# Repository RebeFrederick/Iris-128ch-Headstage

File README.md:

# Iris-128

Open-source 128-channel headstages for neural stimulation and recording.

*The publication of this work can be found at DOI 10.1088/1741-2552/ae1876. The raw data files corresponding to the publication can be found at https://doi.org/10.17605/OSF.IO/XS2PU.*

> [!NOTE]
> Detail documentation and user guides can be found at https://docs.openic.org/iris-128.

| Type | Description |
| :--: | :---------- |
| [Iris-128B](iris-128b/README.md)  | Fully bidirectional headstage with recording or stimulation across all 128 electrode channels. |
| [Iris-128S](iris-128s/README.md) | Selective stimulation headstage with recording from 128 channels and stimulation on 16 simultaneous channels out of 32 available stimulation channels. |
| [Thin-film electrode](thin-film/README.md) | 128 channel surface array used as a test platform for the headstages. |

## File Structure

| Folder  | Description    |
| :-----: | :------------- |
| iris-128b | Project, design, and fabrication files related to Iris-128B Neural Interface System. |
| iris-128s | Project, design, and fabrication files related to Iris-128S Neural Interface System. |
| thin-film    | Design files related to the microelectrode test platform. |
| images    | image files used in README and description files. |

## EDA Tools used in the Development

| EDA Tool     | Version | Usage           |
| :----------: | :-----: | :-------------- |
| KiCad        | 8.0.5   | Design of PCBs. |
| KiCad        | 9.0.3   | Design of PCBs. |
| STM32CubeIDE | 1.16.0  | Design of firmware for MCU. |

## Developers

* Deku Lab, University of Oregon, Eugene, OR
* OpenIC, Eagan, MN

## License

Copyright Manuel Monge, Emma Jacobs 2025.

This source describes Open Hardware and is licensed under CERN-OHL-P v2.

You may redistribute and modify this source and make products using it under the terms of the CERN-OHL-P v2 ([https:/cern.ch/cern-ohl](https:/cern.ch/cern-ohl)). This source is distributed WITHOUT ANY EXPRESS OR IMPLIED WARRANTY, INCLUDING OF MERCHANTABILITY, SATISFACTORY QUALITY AND FITNESS FOR A PARTICULAR PURPOSE. Please see the CERN-OHL-P v2 for applicable conditions.

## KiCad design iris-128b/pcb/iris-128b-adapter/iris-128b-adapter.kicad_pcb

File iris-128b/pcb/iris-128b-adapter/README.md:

# Iris-128B-adapter

*Fig. 1. Adapter connections.*

## Description

`IRIS-128B-ADAPTER`.

### Overview

**Adapter board**.

This is a board with no active components on it. It's purpose is simply to route the connections from the Iris-128B headstage to the power supply, and the four ports on the Intan RHS controller. It also has some header pins intended for testing the SPI connections.

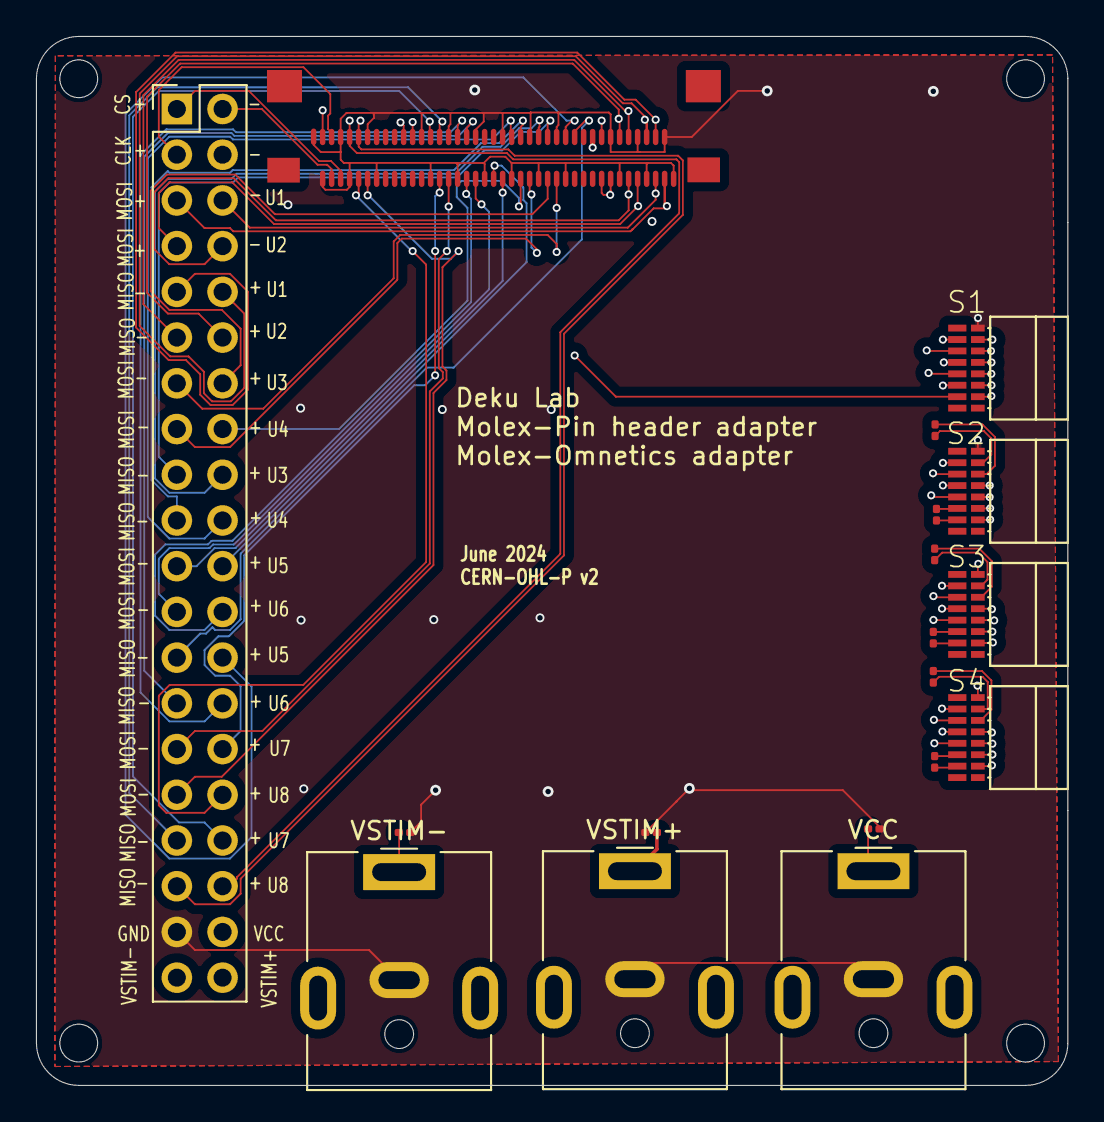
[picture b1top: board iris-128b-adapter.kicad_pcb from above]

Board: 4 copper layers, 57.3 x 58.3 mm, 22 parts (0 on the bottom side), 38 nets.

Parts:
C1, C2, C3: 10 uF; C_0201_0603Metric
H1, H2, H3, H4: MountingHole; MountingHole_2.1mm
J1: Conn_01x40_Pin; PinHeader_2x20_P2.54mm_Vertical
J2: Conn_02x40_Row_Letter_First; molex
R1, R2, R3, R4, R5, R6: R_US; R_0201_0603Metric
S1, S2, S3, S4: OMNETICS_PZN-16-AA
VCC: Barrel_Jack_MountingPin; BarrelJack_CUI_PJ-063AH_Horizontal
VSTIM+: Barrel_Jack_MountingPin; BarrelJack_CUI_PJ-063AH_Horizontal
VSTIM-: Barrel_Jack_MountingPin; BarrelJack_CUI_PJ-063AH_Horizontal

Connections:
/CS+: J1.2, J2.a39, S1.B6 (~CS+)
/CS-: J1.1, J2.a38, S1.B7 (~CS-)
/S1_MISO1+: J1.10, J2.b3, S1.T7 (MISO1+)
/S1_MISO1-: J1.9, J2.b2, S1.T6 (MISO1-)
/S1_MISO2+: J1.12, J2.b6, S1.B2 (MISO2+)
/S1_MISO2-: J1.11, J2.b5, S1.B3 (MISO2-)
/S1_MOSI1+: J1.6, J2.a3, S1.T5 (MOSI1+)
/S1_MOSI1-: J1.5, J2.a2, S1.T4 (MOSI1-)
/S1_MOSI2+: J1.8, J2.a6, S1.B4 (MOSI2+)
/S1_MOSI2-: J1.7, J2.a5, S1.B5 (MOSI2-)
/S2_MISO1+: J1.18, J2.b15, S2.T7 (MISO1+)
/S2_MISO1-: J1.17, J2.b14, S2.T6 (MISO1-)
/S2_MISO2+: J1.20, J2.b18, S2.B2 (MISO2+)
/S2_MISO2-: J1.19, J2.b17, S2.B3 (MISO2-)
/S2_MOSI1+: J1.14, J1.16, J2.a15, J2.a18, S2.B4 (MOSI2+), S2.T5 (MOSI1+)
/S2_MOSI1-: J1.13, J1.15, J2.a14, J2.a17, S2.B5 (MOSI2-), S2.T4 (MOSI1-)
/S3_MISO1+: J1.26, J2.b12, J2.b21, S3.T7 (MISO1+)
/S3_MISO1-: J1.25, J2.b11, J2.b20, S3.T6 (MISO1-)
/S3_MISO2+: J1.28, J2.b24, S3.B2 (MISO2+)
/S3_MISO2-: J1.27, J2.b23, S3.B3 (MISO2-)
/S3_MOSI1+: J1.22, J2.a21, S3.T5 (MOSI1+)
/S3_MOSI1-: J1.21, J2.a20, S3.T4 (MOSI1-)
/S3_MOSI2+: J1.24, J2.a24, S3.B4 (MOSI2+)
/S3_MOSI2-: J1.23, J2.a23, S3.B5 (MOSI2-)
/S4_MISO1+: J1.34, J2.b27, S4.T7 (MISO1+)
/S4_MISO1-: J1.33, J2.b26, S4.T6 (MISO1-)
/S4_MISO2+: J1.36, J2.b36, S4.B2 (MISO2+)
/S4_MISO2-: J1.35, J2.b35, S4.B3 (MISO2-)
/S4_MOSI1+: J1.30, J2.a27, S4.T5 (MOSI1+)
/S4_MOSI1-: J1.29, J2.a26, S4.T4 (MOSI1-)
/S4_MOSI2+: J1.32, J2.a36, S4.B4 (MOSI2+)
/S4_MOSI2-: J1.31, J2.a35, S4.B5 (MOSI2-)
/SCLK+: J1.4, J2.b39, S1.T3 (SCLK+)
/SCLK-: J1.3, J2.b38, S1.T2 (SCLK-)
GND: C1.2, C2.2, C3.2, J1.37, J2.a1, J2.a4, J2.a7, J2.a13, J2.a16, J2.a19, J2.a22, J2.a25, J2.a28, J2.a34, J2.a37, J2.a40, J2.b1, J2.b4, J2.b7, J2.b13, J2.b16, J2.b19, J2.b22, J2.b25, J2.b28, J2.b34, J2.b37, J2.b40, S1.B8 (GND), S2.B8 (GND), S3.B8 (GND), S4.B8 (GND), VCC.2, VSTIM+.2, VSTIM-.2
VCC: C1.1, J1.38, J2.a8, J2.a9, VCC.1
VSTIM+: C2.1, J1.40, J2.b8, J2.b29, VSTIM+.1
VSTIM-: C3.1, J1.39, J2.b9, J2.b30, VSTIM-.1

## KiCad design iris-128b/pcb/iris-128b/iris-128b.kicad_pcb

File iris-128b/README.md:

# Iris-128B
> [!NOTE]
> Detail documentation and user guides can be found at https://docs.openic.org/iris-128/iris-128b.

<br>

*Fig. 1. Iris-128B Neural Interface.*

## Description

### Overview

A **128-channel neural interface capable of stimulation and recording**.

This project develops a system that can stimulate and record from 128 channels using commercially available ICs and integrates into existing commercially available controllers (Intan RHS system). This can be used for small animal, anesthetized electrophysiology, non-human primates, or could be applied to clinical, intraoperative human use cases.

### Iris 128B Architecture

*The Iris 128B system consists of 2 boards: the headstage and the adapter.*

* The **headstage** is a small electronic system placed on top of or near the electrophysiological signals being recorded.
* It uses **commercially available off-the-shelf components**.
* The **adapter board** receives signals from the headstage (through the 80 pin nanopitch Molex connector and cable) and breaks them out into cables that interface with the **Intan Rec/Stim Controller**.

*Fig. 2. System architecture.*

<br>

## Specifications

* Recording and stimulation from all 128 channels.
* Compatible with Intan Recording Controller and Intan Stim/Record Controller.
* *SEAM8 Samtec* connector for interfacing with 128-ch electrode array and compatible with *BlackRock Cereplex E headstages*.
* The *headstage* has a size of 27 x 44 mm$^2$.
* *Molex Nanopitch 76-POS* connector to interface with *Adapter* board through a single cable.
* *Adapter* board draws power from power supply.
* The *adapter* has a size of 57 x 58 mm$^2$.

<br>

## File Structure

### Top Folders: /iris-128b

| Folder  | Subfolders                  | Description    |
| :-----: | :-------------------------- | :------------- |
| pcb | iris-128b <br> iris-128b-adapter <br> libraries | Project, design, and fabrication files related to Iris-128B headstage PCB fabrication and assembly. <br> Project, design, and fabrication files related to Iris-128B adapter PCB fabrication and assembly. <br> Ki-Cad libraries and common files used in PCBs |

<br>

### PCB Folders: /iris-128b/pcb/

| Folder  | Subfolders                  | Description    |
| :-----: | :-------------------------- | :------------- |
| . / |  | Project and design files related to Iris128B. |
| manufacturing |  gerber <br> assembly <br> bom | Gerber files for fabrication of `Iris-PCB`. <br> Assembly files for `Iris-PCB`. <br> Bill of Materials for `Iris-PCB`. |

<br>

## File Types

| File | Folder | Description |
| :--- | :----- | :---------- |
| README.md | iris-128x | Description of Iris-128X system. |
| kicad-files | iris-128x / pcb / | Ki-Cad project and design files. |
| gerber-files | iris-128x / pcb / manufacturing / gerber | Gerber files. |
| iris-128x-all-pos.csv | iris-128x / pcb / manufacturing / assembly | Assembly files in `csv` format.|
| iris-128x_bom.csv | iris-128x / pcb / manufacturing / bom | Bill of materials in `csv` format. |
| symbol-libraries | iris-128x / pcb / libraries | Ki-Cad symbol libraries used in PCBs. |
| footprint-libraries | iris-128x / pcb / libraries | Ki-Cad footprint libraries used in PCBs. |

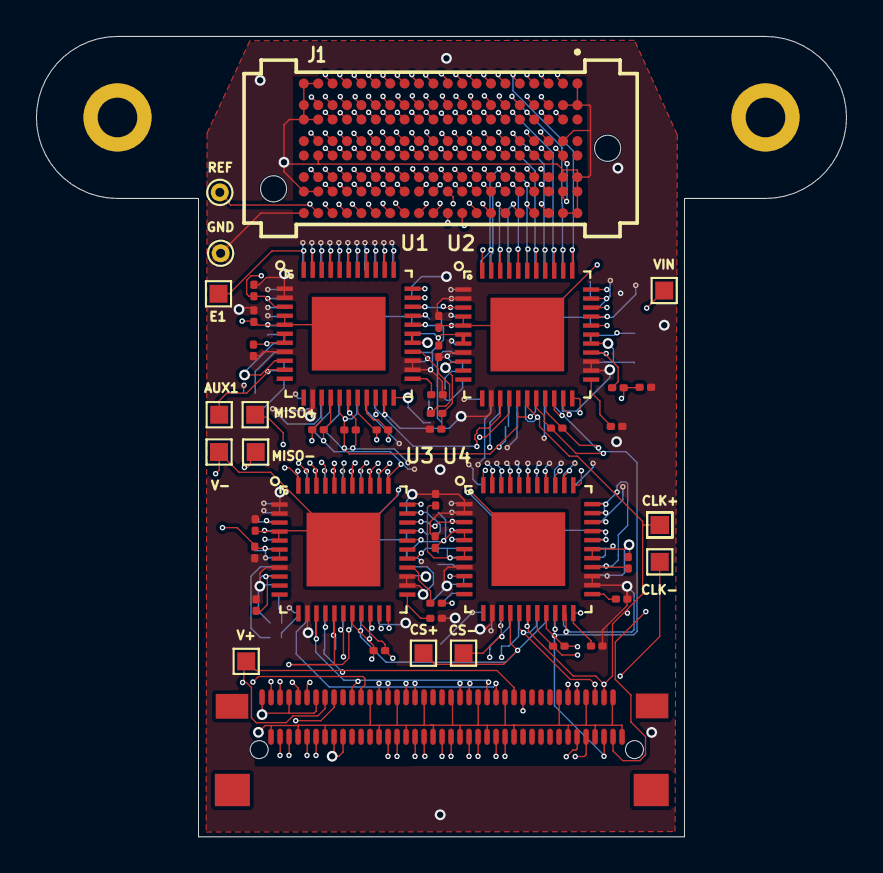
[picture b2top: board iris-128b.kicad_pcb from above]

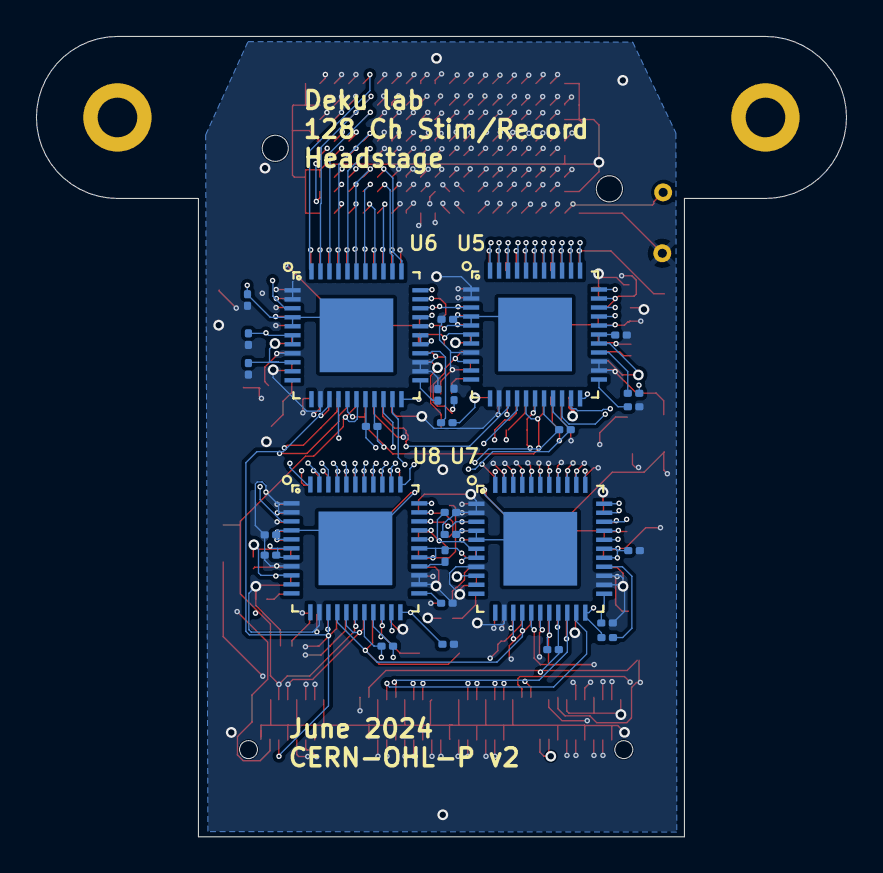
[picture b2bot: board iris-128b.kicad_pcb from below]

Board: 8 copper layers, 45.0 x 44.5 mm, 77 parts (28 on the bottom side), 184 nets.

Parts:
AUX1: TestPoint; TestPoint_Pad_1.0x1.0mm
C1, C2, C3, C4, C5, C6, C7, C8, C9, C10, C11, C12, C13, C14, C15, C16, C17, C18, C19, C20, C21, C22, C23, C24: 100 nF; C_0201_0603Metric
C25, C26, C27, C28, C29, C30, C31, C32: 10 nF; C_0201_0603Metric
CLK+: TestPoint; TestPoint_Pad_1.0x1.0mm
CLK+#2: TestPoint; TestPoint_Pad_1.0x1.0mm
CLK-: TestPoint; TestPoint_Pad_1.0x1.0mm
CS+: TestPoint; TestPoint_Pad_1.0x1.0mm
CS-: TestPoint; TestPoint_Pad_1.0x1.0mm
E1: TestPoint; TestPoint_Pad_1.0x1.0mm
GND: TESTPOINT_SMALL; TestPoint_THTPad_D1.0mm_Drill0.5mm
H1, H2: MountingHole; MountingHole_2.2mm_M2_DIN965_Pad
J1: SEAM8-20-S02.0-X-08-3; SAMTEC_SEAM8-20-S02.0-X-08-3
J2: Conn_02x40_Row_Letter_First; molex
LVDS1, LVDS2, LVDS3, LVDS4, LVDS5, LVDS6, LVDS7, LVDS8: 0; R_0201_0603Metric
MISO+: TestPoint; TestPoint_Pad_1.0x1.0mm
MISO-: TestPoint; TestPoint_Pad_1.0x1.0mm
R1: 0; R_0201_0603Metric
R2, R3, R4, R5, R6, R7, R8, R9, R10, R11: 100; R_0201_0603Metric
REF: TESTPOINT_SMALL; TestPoint_THTPad_D1.0mm_Drill0.5mm
U1, U2, U3, U4, U5, U6, U7, U8: QFN44_7_X_7
V+: TestPoint; TestPoint_Pad_1.0x1.0mm
V-: TestPoint; TestPoint_Pad_1.0x1.0mm
VIN: VCC; TestPoint_Pad_1.0x1.0mm

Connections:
/CS+: CS+.1, J2.b39, R10.1, U1.15 (~CS+), U2.15 (~CS+), U3.15 (~CS+), U4.15 (~CS+), U5.15 (~CS+), U6.15 (~CS+), U7.15 (~CS+), U8.15 (~CS+)
/CS-: CS-.1, J2.b38, R10.2, U1.14 (~CS-), U2.14 (~CS-), U3.14 (~CS-), U4.14 (~CS-), U5.14 (~CS-), U6.14 (~CS-), U7.14 (~CS-), U8.14 (~CS-)
/Chip1-Elec0: E1.1, J1.C1-E0 (A01), U1.44 (ELEC0)
/Chip1-Elec1: J1.C1-E1 (A02), U1.43 (ELEC1)
/Chip1-Elec2: J1.C1-E2 (B01), U1.42 (ELEC2)
/Chip1-Elec3: J1.C1-E3 (B02), U1.41 (ELEC3)
/Chip1-Elec4: J1.C1-E4 (C01), U1.40 (ELEC4)
/Chip1-Elec5: J1.C1-E5 (C02), U1.39 (ELEC5)
/Chip1-Elec6: J1.C1-E6 (D01), U1.38 (ELEC6)
/Chip1-Elec7: J1.C1-E7 (D02), U1.37 (ELEC7)
/Chip1-Elec8: J1.C1-E8 (A03), U1.36 (ELEC8)
/Chip1-Elec9: J1.C1-E9 (A04), U1.35 (ELEC9)
/Chip1-Elec10: J1.C1-E10 (B03), U1.34 (ELEC10)
/Chip1-Elec11: J1.C1-E11 (B04), U1.33 (ELEC11)
/Chip1-Elec12: J1.C1-E12 (C03), U1.32 (ELEC12)
/Chip1-Elec13: J1.C1-E13 (C04), U1.31 (ELEC13)
/Chip1-Elec14: J1.C1-E14 (D03), U1.30 (ELEC14)
/Chip1-Elec15: J1.C1-E15 (D04), U1.29 (ELEC15)
/Chip2-Elec0: J1.C2-E0 (A27), U2.44 (ELEC0)
/Chip2-Elec1: J1.C2-E1 (A28), U2.43 (ELEC1)
/Chip2-Elec2: J1.C2-E2 (B27), U2.42 (ELEC2)
/Chip2-Elec3: J1.C2-E3 (B28), U2.41 (ELEC3)
/Chip2-Elec4: J1.C2-E4 (C27), U2.40 (ELEC4)
/Chip2-Elec5: J1.C2-E5 (C28), U2.39 (ELEC5)
/Chip2-Elec6: J1.C2-E6 (D27), U2.38 (ELEC6)
/Chip2-Elec8: J1.C2-E8 (D26), U2.36 (ELEC8)
/Chip2-Elec9: J1.C2-E9 (D25), U2.35 (ELEC9)
/Chip2-Elec10: J1.C2-E10 (C26), U2.34 (ELEC10)
/Chip2-Elec11: J1.C2-E11 (C25), U2.33 (ELEC11)
/Chip2-Elec12: J1.C2-E12 (B26), U2.32 (ELEC12)
/Chip2-Elec13: J1.C2-E13 (B25), U2.31 (ELEC13)
/Chip2-Elec14: J1.C2-E14 (A26), U2.30 (ELEC14)
/Chip2-Elec15: J1.C2-E15 (A25), U2.29 (ELEC15)
/Chip3-Elec0: J1.C3-E0 (NC), U3.44 (ELEC0)
/Chip3-Elec1: J1.C3-E1 (NC), U3.43 (ELEC1)
/Chip3-Elec2: J1.C3-E2 (NC), U3.42 (ELEC2)
/Chip3-Elec3: J1.C3-E3 (NC), U3.41 (ELEC3)
/Chip3-Elec4: J1.C3-E4 (C09), U3.40 (ELEC4)
/Chip3-Elec5: J1.C3-E5 (C10), U3.39 (ELEC5)
/Chip3-Elec6: J1.C3-E6 (D09), U3.38 (ELEC6)
/Chip3-Elec7: J1.C3-E7 (D10), U3.37 (ELEC7)
/Chip3-Elec8: J1.C3-E8 (A11), U3.36 (ELEC8)
/Chip3-Elec9: J1.C3-E9 (A12), U3.35 (ELEC9)
/Chip3-Elec10: J1.C3-E10 (D12), U3.34 (ELEC10)
/Chip3-Elec11: J1.C3-E11 (D11), U3.33 (ELEC11)
/Chip3-Elec12: J1.C3-E12 (C12), U3.32 (ELEC12)
/Chip3-Elec13: J1.C3-E13 (C11), U3.31 (ELEC13)
/Chip3-Elec14: J1.C3-E14 (B12), U3.30 (ELEC14)
/Chip3-Elec15: J1.C3-E15 (B11), U3.29 (ELEC15)
/Chip4-Elec0: J1.C4-E0 (A20), U4.44 (ELEC0)
/Chip4-Elec1: J1.C4-E1 (A22), U4.43 (ELEC1)
/Chip4-Elec2: J1.C4-E2 (A24), U4.42 (ELEC2)
/Chip4-Elec3: J1.C4-E3 (B17), U4.41 (ELEC3)
/Chip4-Elec4: J1.C4-E4 (B19), U4.40 (ELEC4)
/Chip4-Elec5: J1.C4-E5 (B21), U4.39 (ELEC5)
/Chip4-Elec6: J1.C4-E6 (B23), U4.38 (ELEC6)
/Chip4-Elec7: J1.C4-E7 (B20), U4.37 (ELEC7)
/Chip4-Elec8: J1.C4-E8 (B22), U4.36 (ELEC8)
/Chip4-Elec9: J1.C4-E9 (B24), U4.35 (ELEC9)
/Chip4-Elec10: J1.C4-E10 (C23), U4.34 (ELEC10)
/Chip4-Elec11: J1.C4-E11 (A18), U4.33 (ELEC11)
/Chip4-Elec12: J1.C4-E12 (A23), U4.32 (ELEC12)
/Chip4-Elec13: J1.C4-E13 (A21), U4.31 (ELEC13)
/Chip4-Elec14: J1.C4-E14 (A19), U4.30 (ELEC14)
/Chip4-Elec15: J1.C4-E15 (A17), U4.29 (ELEC15)
/Chip5-Elec0: J1.C5-E0 (A08), U5.44 (ELEC0)
/Chip5-Elec1: J1.C5-E1 (B07), U5.43 (ELEC1)
/Chip5-Elec2: J1.C5-E2 (B08), U5.42 (ELEC2)
/Chip5-Elec3: J1.C5-E3 (C07), U5.41 (ELEC3)
/Chip5-Elec4: J1.C5-E4 (C08), U5.40 (ELEC4)
/Chip5-Elec5: J1.C5-E5 (D07), U5.39 (ELEC5)
/Chip5-Elec6: J1.C5-E6 (D08), U5.38 (ELEC6)
/Chip5-Elec7: J1.C5-E7 (A07), U5.37 (ELEC7)
/Chip5-Elec8: J1.C5-E8 (D06), U5.36 (ELEC8)
/Chip5-Elec9: J1.C5-E9 (D05), U5.35 (ELEC9)
/Chip5-Elec10: J1.C5-E10 (C06), U5.34 (ELEC10)
/Chip5-Elec11: J1.C5-E11 (C05), U5.33 (ELEC11)
/Chip5-Elec12: J1.C5-E12 (B06), U5.32 (ELEC12)
/Chip5-Elec13: J1.C5-E13 (B05), U5.31 (ELEC13)
/Chip5-Elec14: J1.C5-E14 (A06), U5.30 (ELEC14)
/Chip5-Elec15: J1.C5-E15 (A05), U5.29 (ELEC15)
/Chip6-Elec0: J1.C6-E0 (D28), U6.44 (ELEC0)
/Chip6-Elec1: J1.C6-E1 (D27), U6.43 (ELEC1)
/Chip6-Elec2: J1.C6-E2 (C28), U6.42 (ELEC2)
/Chip6-Elec3: J1.C6-E3 (C27), U6.41 (ELEC3)
/Chip6-Elec4: J1.C6-E4 (B28), U6.40 (ELEC4)
/Chip6-Elec5: J1.C6-E5 (B27), U6.39 (ELEC5)
/Chip6-Elec6: J1.C6-E6 (A28), U6.38 (ELEC6)
/Chip6-Elec7: J1.C6-E7 (A27), U6.37 (ELEC7)
/Chip6-Elec8: J1.C6-E8 (D26), U6.36 (ELEC8)
/Chip6-Elec9: J1.C6-E9 (D25), U6.35 (ELEC9)
/Chip6-Elec10: J1.C6-E10 (C26), U6.34 (ELEC10)
/Chip6-Elec11: J1.C6-E11 (A26), U6.33 (ELEC11)
/Chip6-Elec12: J1.C6-E12 (B25), U6.32 (ELEC12)
/Chip6-Elec13: J1.C6-E13 (B26), U6.31 (ELEC13)
/Chip6-Elec14: J1.C6-E14 (C25), U6.30 (ELEC14)
/Chip6-Elec15: J1.C6-E15 (A25), U6.29 (ELEC15)
/Chip7-Elec0: J1.C7-E0 (C16), U7.44 (ELEC0)
/Chip7-Elec1: J1.C7-E1 (D15), U7.43 (ELEC1)
/Chip7-Elec2: J1.C7-E2 (D16), U7.42 (ELEC2)
/Chip7-Elec3: J1.C7-E3 (D14), U7.41 (ELEC3)
/Chip7-Elec4: J1.C7-E4 (D13), U7.40 (ELEC4)
/Chip7-Elec5: J1.C7-E5 (C14), U7.39 (ELEC5)
/Chip7-Elec6: J1.C7-E6 (C13), U7.38 (ELEC6)
/Chip7-Elec7: J1.C7-E7 (B14), U7.37 (ELEC7)
/Chip7-Elec8: J1.C7-E8 (B13), U7.36 (ELEC8)
/Chip7-Elec9: J1.C7-E9 (A14), U7.35 (ELEC9)
/Chip7-Elec10: J1.C7-E10 (A13), U7.34 (ELEC10)
/Chip7-Elec11: J1.C7-E11 (A15), U7.33 (ELEC11)
/Chip7-Elec12: J1.C7-E12 (A16), U7.32 (ELEC12)
/Chip7-Elec13: J1.C7-E13 (B15), U7.31 (ELEC13)
/Chip7-Elec14: J1.C7-E14 (B16), U7.30 (ELEC14)
/Chip7-Elec15: J1.C7-E15 (C15), U7.29 (ELEC15)
/Chip8-Elec0: J1.C8-E0 (C21), U8.44 (ELEC0)
/Chip8-Elec1: J1.C8-E1 (C19), U8.43 (ELEC1)
/Chip8-Elec2: J1.C8-E2 (C24), U8.42 (ELEC2)
/Chip8-Elec3: J1.C8-E3 (C22), U8.41 (ELEC3)
/Chip8-Elec4: J1.C8-E4 (C20), U8.40 (ELEC4)
/Chip8-Elec5: J1.C8-E5 (D23), U8.39 (ELEC5)
/Chip8-Elec6: J1.C8-E6 (D21), U8.38 (ELEC6)
/Chip8-Elec7: J1.C8-E7 (D19), U8.37 (ELEC7)
/Chip8-Elec8: J1.C8-E8 (D24), U8.36 (ELEC8)
/Chip8-Elec9: J1.C8-E9 (D22), U8.35 (ELEC9)
/Chip8-Elec10: J1.C8-E10 (D20), U8.34 (ELEC10)
/Chip8-Elec11: J1.C8-E11 (B18), U8.33 (ELEC11)
/Chip8-Elec12: J1.C8-E12 (C17), U8.32 (ELEC12)
/Chip8-Elec13: J1.C8-E13 (C18), U8.31 (ELEC13)
/Chip8-Elec14: J1.C8-E14 (D17), U8.30 (ELEC14)
/Chip8-Elec15: J1.C8-E15 (D18), U8.29 (ELEC15)
/Net-(CHIP1-MISO+): J2.a3, MISO+.1, U1.21 (MISO+)
/Net-(CHIP1-MISO-): J2.a2, MISO-.1, U1.20 (MISO-)
/Net-(CHIP1-MOSI+): J2.b3, R2.2, U1.19 (MOSI+)
/Net-(CHIP1-MOSI-): J2.b2, R2.1, U1.18 (MOSI-)
/Net-(CHIP2-MISO+): J2.a6, U2.21 (MISO+)
/Net-(CHIP2-MISO-): J2.a5, U2.20 (MISO-)
/Net-(CHIP2-MOSI+): J2.b6, R3.2, U2.19 (MOSI+)
/Net-(CHIP2-MOSI-): J2.b5, R3.1, U2.18 (MOSI-)
/Net-(CHIP3-MOSI+): J2.b15, R4.2, U3.19 (MOSI+)
/Net-(CHIP3-MOSI-): J2.b14, R4.1, U3.18 (MOSI-)
/Net-(CHIP4-MOSI+): J2.b18, R5.2, U4.19 (MOSI+)
/Net-(CHIP4-MOSI-): J2.b17, R5.1, U4.18 (MOSI-)
/Net-(CHIP5-MOSI+): J2.b21, R6.2, U5.19 (MOSI+)
/Net-(CHIP5-MOSI-): J2.b20, R6.1, U5.18 (MOSI-)
/Net-(CHIP6-MOSI+): J2.b24, R7.2, U6.19 (MOSI+)
/Net-(CHIP6-MOSI-): J2.b23, R7.1, U6.18 (MOSI-)
/Net-(CHIP7-MOSI+): J2.b27, R8.2, U7.19 (MOSI+)
/Net-(CHIP7-MOSI-): J2.b26, R8.1, U7.18 (MOSI-)
/Net-(CHIP8-MOSI+): J2.b36, R9.2, U8.19 (MOSI+)
/Net-(CHIP8-MOSI-): J2.b35, R9.1, U8.18 (MOSI-)
/Net-(U1-REF_ELEC): J1.R1, J1.R2 (NC), R1.2, REF.1
/SCLK+: CLK+.1, CLK+#2.1, J2.a39, R11.2, U1.17 (SCLK+), U2.17 (SCLK+), U3.17 (SCLK+), U4.17 (SCLK+), U5.17 (SCLK+), U6.17 (SCLK+), U7.17 (SCLK+), U8.17 (SCLK+)
/SCLK-: CLK-.1, J2.a38, R11.1, U1.16 (SCLK-), U2.16 (SCLK-), U3.16 (SCLK-), U4.16 (SCLK-), U5.16 (SCLK-), U6.16 (SCLK-), U7.16 (SCLK-), U8.16 (SCLK-)
CHIP3-MISO+: J2.a15, U3.21 (MISO+)
CHIP3-MISO-: J2.a14, U3.20 (MISO-)
CHIP4-MISO+: J2.a18, U4.21 (MISO+)
CHIP4-MISO-: J2.a17, U4.20 (MISO-)
CHIP5-MISO+: J2.a12, U5.21 (MISO+)
CHIP5-MISO-: J2.a11, U5.20 (MISO-)
CHIP6-MISO+: J2.a24, U6.21 (MISO+)
CHIP6-MISO-: J2.a23, U6.20 (MISO-)
CHIP7-MISO+: J2.a27, U7.21 (MISO+)
CHIP7-MISO-: J2.a26, U7.20 (MISO-)
CHIP8-MISO+: J2.a36, U8.21 (MISO+)
CHIP8-MISO-: J2.a35, U8.20 (MISO-)
GND: C1.2, C2.2, C3.2, C4.2, C5.2, C6.2, C7.2, C8.2, C9.2, C10.2, C11.2, C12.2, C13.2, C14.2, C15.2, C16.2, C17.2, C18.2, C19.2, C20.2, C21.2, C22.2, C23.2, C24.2, C25.2, C26.2, C27.2, C28.2, C29.2, C30.2, C31.2, C32.2, J1.G, J2.a1, J2.a4, J2.a7, J2.a13, J2.a16, J2.a19, J2.a22, J2.a25, J2.a28, J2.a34, J2.a37, J2.a40, J2.b1, J2.b4, J2.b7, J2.b13, J2.b16, J2.b19, J2.b22, J2.b25, J2.b28, J2.b34, J2.b37, J2.b40, R1.1, U1.1 (STIM_GND), U1.2 (SENSE_GND), U1.8 (GND1), U1.13 (GND2), U1.24 (GND3), U1.25 (GND4), U2.1 (STIM_GND), U2.2 (SENSE_GND), U2.8 (GND1), U2.13 (GND2), U2.24 (GND3), U2.25 (GND4), U3.1 (STIM_GND), U3.2 (SENSE_GND), U3.8 (GND1), U3.13 (GND2), U3.24 (GND3), U3.25 (GND4), U4.1 (STIM_GND), U4.2 (SENSE_GND), U4.8 (GND1), U4.13 (GND2), U4.24 (GND3), U4.25 (GND4), U5.1 (STIM_GND), U5.2 (SENSE_GND), U5.8 (GND1), U5.13 (GND2), U5.24 (GND3), U5.25 (GND4), U6.1 (STIM_GND), U6.2 (SENSE_GND), U6.8 (GND1), U6.13 (GND2), U6.24 (GND3), U6.25 (GND4), U7.1 (STIM_GND), U7.2 (SENSE_GND), U7.8 (GND1), U7.13 (GND2), U7.24 (GND3), U7.25 (GND4), U8.1 (STIM_GND), U8.2 (SENSE_GND), U8.8 (GND1), U8.13 (GND2), U8.24 (GND3), U8.25 (GND4)
unnamed: C25.1, U1.23 (ADC_REF)
unnamed: LVDS1.1, U1.26 (LVDS_EN)
unnamed: C26.1, U2.23 (ADC_REF)
unnamed: LVDS2.1, U2.26 (LVDS_EN)
unnamed: C27.1, U3.23 (ADC_REF)
unnamed: LVDS3.1, U3.26 (LVDS_EN)
unnamed: C28.1, U4.23 (ADC_REF)
unnamed: LVDS4.1, U4.26 (LVDS_EN)
unnamed: C29.1, U5.23 (ADC_REF)
unnamed: LVDS5.1, U5.26 (LVDS_EN)
unnamed: C30.1, U6.23 (ADC_REF)
unnamed: LVDS6.1, U6.26 (LVDS_EN)
unnamed: C31.1, U7.23 (ADC_REF)
unnamed: LVDS7.1, U7.26 (LVDS_EN)
unnamed: C32.1, U8.23 (ADC_REF)
unnamed: LVDS8.1, U8.26 (LVDS_EN)
V+: C1.1, C2.1, C3.1, C4.1, C5.1, C6.1, C7.1, C8.1, J2.a8, J2.a29, U1.6 (VSTIM+1), U1.7 (VSTIM+2), U2.6 (VSTIM+1), U2.7 (VSTIM+2), U3.6 (VSTIM+1), U3.7 (VSTIM+2), U4.6 (VSTIM+1), U4.7 (VSTIM+2), U5.6 (VSTIM+1), U5.7 (VSTIM+2), U6.6 (VSTIM+1), U6.7 (VSTIM+2), U7.6 (VSTIM+1), U7.7 (VSTIM+2), U8.6 (VSTIM+1), U8.7 (VSTIM+2), V+.1
V-: C17.1, C18.1, C19.1, C20.1, C21.1, C22.1, C23.1, C24.1, J2.a9, J2.a30, U1.4 (VSTIM-1), U1.5 (VSTIM-2), U1.CENTER (VSTIM-), U2.4 (VSTIM-1), U2.5 (VSTIM-2), U2.CENTER (VSTIM-), U3.4 (VSTIM-1), U3.5 (VSTIM-2), U3.CENTER (VSTIM-), U4.4 (VSTIM-1), U4.5 (VSTIM-2), U4.CENTER (VSTIM-), U5.4 (VSTIM-1), U5.5 (VSTIM-2), U5.CENTER (VSTIM-), U6.4 (VSTIM-1), U6.5 (VSTIM-2), U6.CENTER (VSTIM-), U7.4 (VSTIM-1), U7.5 (VSTIM-2), U7.CENTER (VSTIM-), U8.4 (VSTIM-1), U8.5 (VSTIM-2), U8.CENTER (VSTIM-), V-.1
VCC: C9.1, C10.1, C11.1, C12.1, C13.1, C14.1, C15.1, C16.1, J2.b8, J2.b9, LVDS1.2, LVDS2.2, LVDS3.2, LVDS4.2, LVDS5.2, LVDS6.2, LVDS7.2, LVDS8.2, U1.9 (STIM_EN), U1.22 (VDD1), U1.27 (VDD2), U1.28 (VDD3), U2.9 (STIM_EN), U2.22 (VDD1), U2.27 (VDD2), U2.28 (VDD3), U3.9 (STIM_EN), U3.22 (VDD1), U3.27 (VDD2), U3.28 (VDD3), U4.9 (STIM_EN), U4.22 (VDD1), U4.27 (VDD2), U4.28 (VDD3), U5.9 (STIM_EN), U5.22 (VDD1), U5.27 (VDD2), U5.28 (VDD3), U6.9 (STIM_EN), U6.22 (VDD1), U6.27 (VDD2), U6.28 (VDD3), U7.9 (STIM_EN), U7.22 (VDD1), U7.27 (VDD2), U7.28 (VDD3), U8.9 (STIM_EN), U8.22 (VDD1), U8.27 (VDD2), U8.28 (VDD3), VIN.1

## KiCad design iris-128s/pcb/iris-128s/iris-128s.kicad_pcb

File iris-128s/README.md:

# Iris-128S
> [!NOTE]
> Detail documentation and user guides can be found at https://docs.openic.org/iris-128/iris-128s.

<br>

<p style="text-align:center"><i><b>Figure 1.</b> Iris-128S Neural Interface.</i></p>

<br>

## Description

The Iris-128S neural interface consists of 2 boards: the *headstage* and the *adapter*. The *headstage* is a small electronic board that is normally placed on top of or nearby the animal model being studied. It has been designed to be as small as possible while using standard, commercially available off-the-shelf components. The *adapter* is a small electronic board which has been designed to interface with the Intan Recording Controller, the Intan Rec/Stim Controller, and a programmer/computer to program the switches in the *headstage* via a MCU.

The architecture and schematic of Iris-128S are shown in the figures below.

```mermaid
graph LR
    c0["128-Ch
        Electrode
        Array"]
    c1["`**Headstage**`"]
    c2["`**Adapter**`"]
    c3["Intan Rec
        Controller"]
    c4["Intan Rec/Stim
        Controller"]
    c5["Programmer"]
    c0 <--> c1
    c1 <----> c2
    c2 <--> c3
    c2 <--> c4
    c2 <--> c5
```
<p style="text-align:center"><i><b>Figure 2.</b> System Architecture of Iris-128S.</i></p>

<br>

<p style="text-align:center"><i><b>Figure 3.</b> Schematic of Iris-128S.</i></p>

<br>

## Specifications

* Recording from all 128 channels.
* Stimulation from 32 designated channels, where up to 16 of them can be selected for simultaneous stimulation.
* Compatible with Intan Recording Controller and Intan Stim/Record Controller.
* *SEAM8 Samtec* connector for interfacing with 128-ch electrode array and compatible with *BlackRock Cereplex E headstages*.
* The *headstage* has a size of 30.2 x 25.5 mm$^2$.
* *Omnetics 36-POS* connector to interface with *Adapter* board through a single cable.
* *Adapter* board draws power directly from the Intan Recording Controller to power itself and the *headstage*.
* On-board power management unit (PMU) in the *Adapter* board generates the required supplies for the MCU and *ADGS5414* switches.
* Programmer in the *Adapter* board is only needed to update the firmware in the MCU, i.e., change the state of the *ADGS5414* switches. After MCU is programmed, only the Intan controlleres are needed.
* The *adapter* has a size of 50 x 40 mm$^2$.

<br>

## File Structure

### Top Folders: /iris-128s

| Folder  | Subfolders                  | Description    |
| :-----: | :-------------------------- | :------------- |
| pcb | iris-128s <br> iris-128s-adapter <br> libraries <br> datasheets | Project, design, and fabrication files related to Iris-128S headstage PCB fabrication and assembly. <br> Project, design, and fabrication files related to Iris-128S adapter PCB fabrication and assembly. <br> Ki-Cad libraries and common files used in PCBs <br> Datasheets of components used in PCBs. |
| mcu | controller | Project and firmware files related to MCU programming. |

<br>

### PCB Folders: /iris-128s/pcb/`Iris-PCB`

| Folder  | Subfolders                  | Description    |
| :-----: | :-------------------------- | :------------- |
| . / |  | Project and design files related to `Iris-PCB`. |
| manufacturing |  gerber <br> assembly <br> bom | Gerber files for fabrication of `Iris-PCB`. <br> Assembly files for `Iris-PCB`. <br> Bill of Materials for `Iris-PCB`. |

<br>

### MCU Folders: /iris-128s/mcu

| Folder  | Subfolders                  | Description    |
| :-----: | :-------------------------- | :------------- |
| controller | Core / Inc <br> Core / Src <br> Core / Startup <br> Debug <br> Drivers | `C` library files. <br> `C` source files. <br> Assembly startup file. <br> Debug-related files. <br> Driver files for target MCU. |

<br>

## File Types

| File | Folder | Description |
| :--- | :----- | :---------- |
| README.md | iris-128x | Description of Iris-128X system. |
| pcb-fab-specs.md | iris-128x / pcb | Specifications for the fabricatin of `Iris-PCB`.
| kicad-files | iris-128x / pcb / `Iris-PCB` | Ki-Cad project and design files. |
| iris-128x-schematic.pdf | iris-128x / pcb / `Iris-PCB` | PDF of PCB schematic. |
| gerber-files | iris-128x / pcb / `Iris-PCB` / manufacturing / gerber | Gerber files. |
| iris-128x-all-pos.csv | iris-128x / pcb / `Iris-PCB` / manufacturing / assembly | Assembly files in `csv` format. |
| iris-128x_bom.csv | iris-128x / pcb / `Iris-PCB` / manufacturing / bom | Bill of materials in `csv` format. |
| datasheet-files.pdf | iris-128x / pcb / datasheets | PDFs of the datasheets of all components used in PCBs. |
| symbol-libraries | iris-128x / pcb / libraries | Ki-Cad symbol libraries used in PCBs. |
| footprint-libraries | iris-128x / pcb / libraries | Ki-Cad footprint libraries used in PCBs. |
| main.c | iris-128s / mcu / controller / Core / Src | Main `C` file running on MCU. |
| c-files | iris-128s / mcu / controller / Core | `C` files related to MCU firmware. |
| c-files | iris-128s / mcu / controller / Debug | `C` files related to MCU debugging. |
| c-files | iris-128s / mcu / controller / Drivers | `C` file related to MCU drivers. |
| .*project | iris-128s / mcu / controller | STM32CubeIDE project-related files. |
| *.launch | iris-128s / mcu / controller | STM32CubeIDE debug-related files. |
| *.ioc | iris-128s / mcu / controller | STM32CubeIDE MCU system configuration file. |
| *.id | iris-128s / mcu / controller | STM32CubeIDE MCU memory configuration file. |

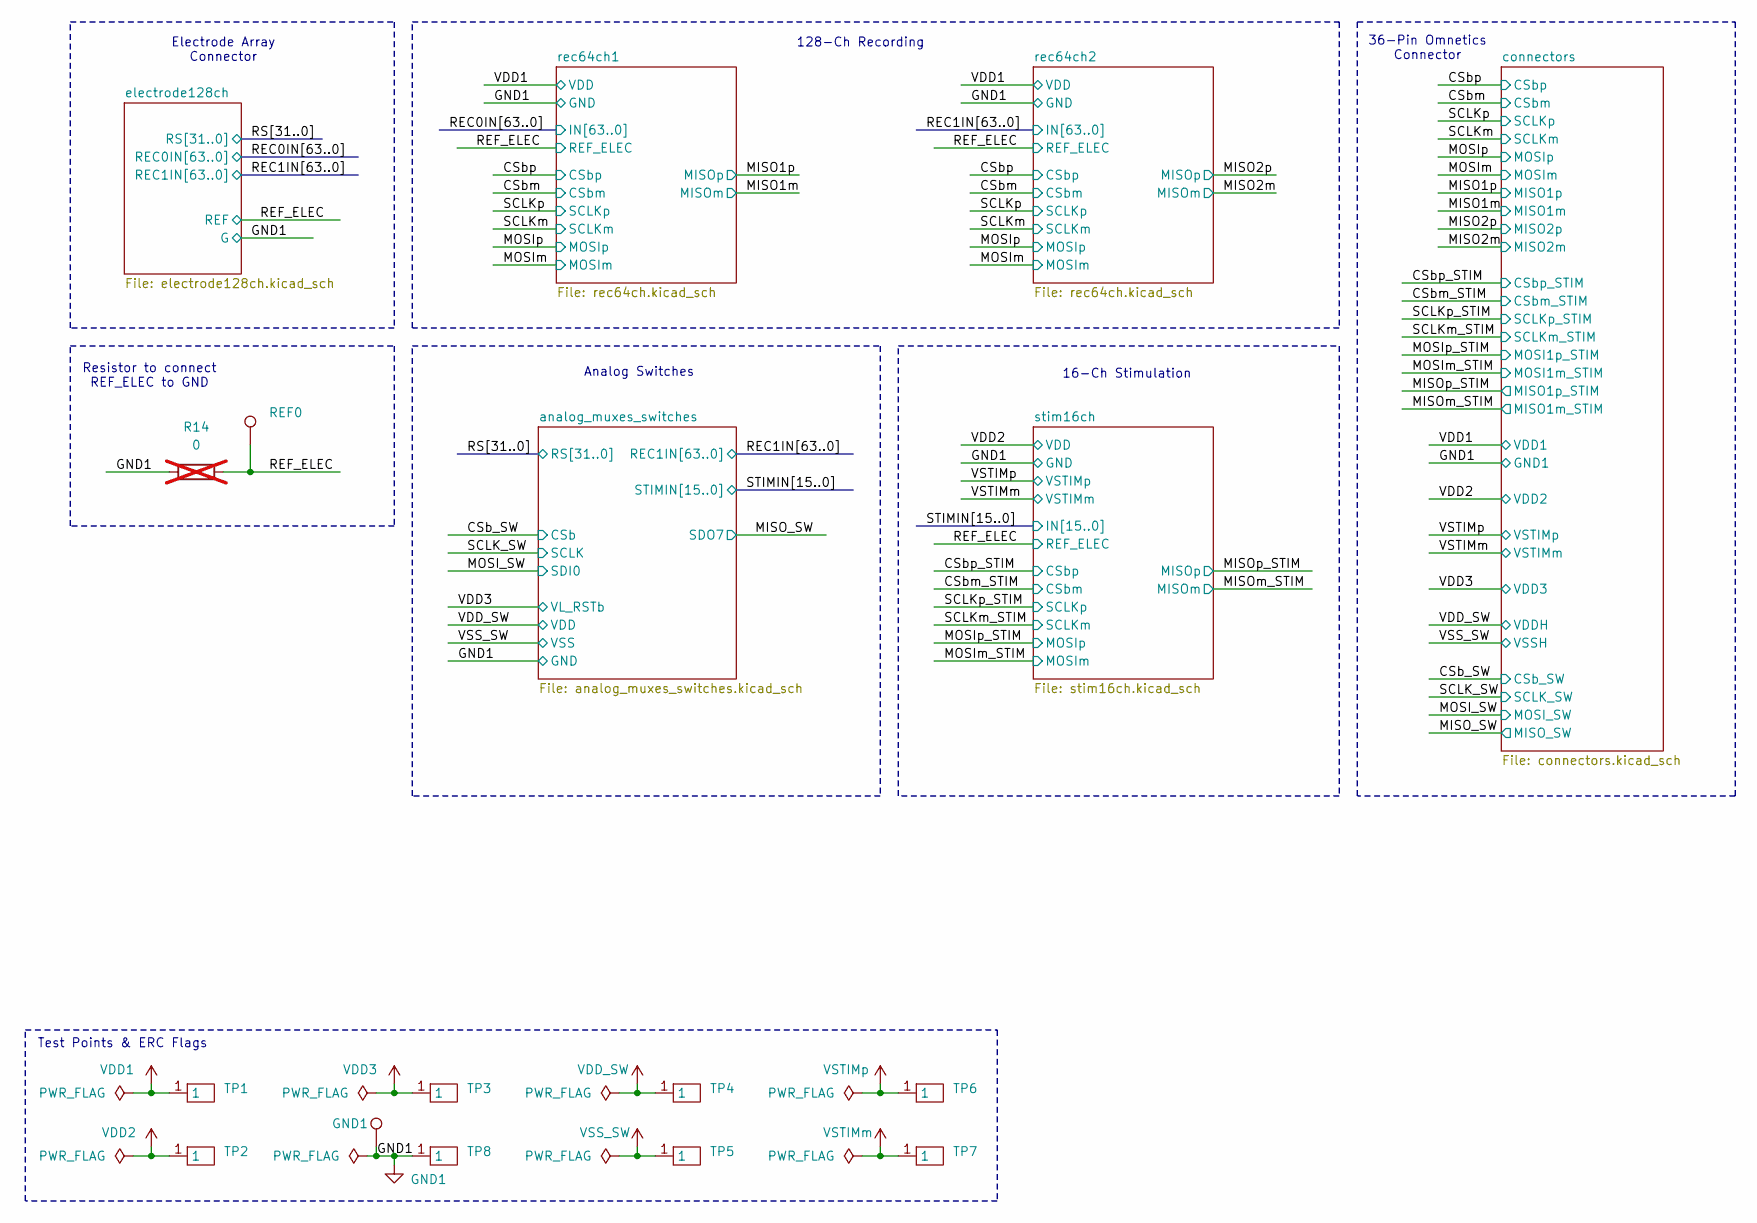
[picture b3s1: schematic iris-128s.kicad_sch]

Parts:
GND1: GND1; TESTPOINT_SMALL
R14: 0; R_0402_1005Metric; not fitted
REF0: REF0; TESTPOINT_SMALL
TP1, TP2, TP3, TP4, TP5, TP6, TP7, TP8: TESTPOINT_PAD_SQ_0.5

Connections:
/REF_ELEC: R14.2, REF0.1; also elsewhere on the board
GND1: GND1.1, R14.1, TP8.1; also elsewhere on the board
VDD1: TP1.1; also elsewhere on the board
VDD2: TP2.1; also elsewhere on the board
VDD3: TP3.1; also elsewhere on the board
VDD_SW: TP4.1; also elsewhere on the board
VSS_SW: TP5.1; also elsewhere on the board
VSTIMm: TP7.1; also elsewhere on the board
VSTIMp: TP6.1; also elsewhere on the board

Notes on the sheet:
Resistor to connect REF_ELEC to GND
Analog Switches
16-Ch Stimulation
128-Ch Recording
Electrode Array Connector
Test Points & ERC Flags
36-Pin Omnetics Connector
